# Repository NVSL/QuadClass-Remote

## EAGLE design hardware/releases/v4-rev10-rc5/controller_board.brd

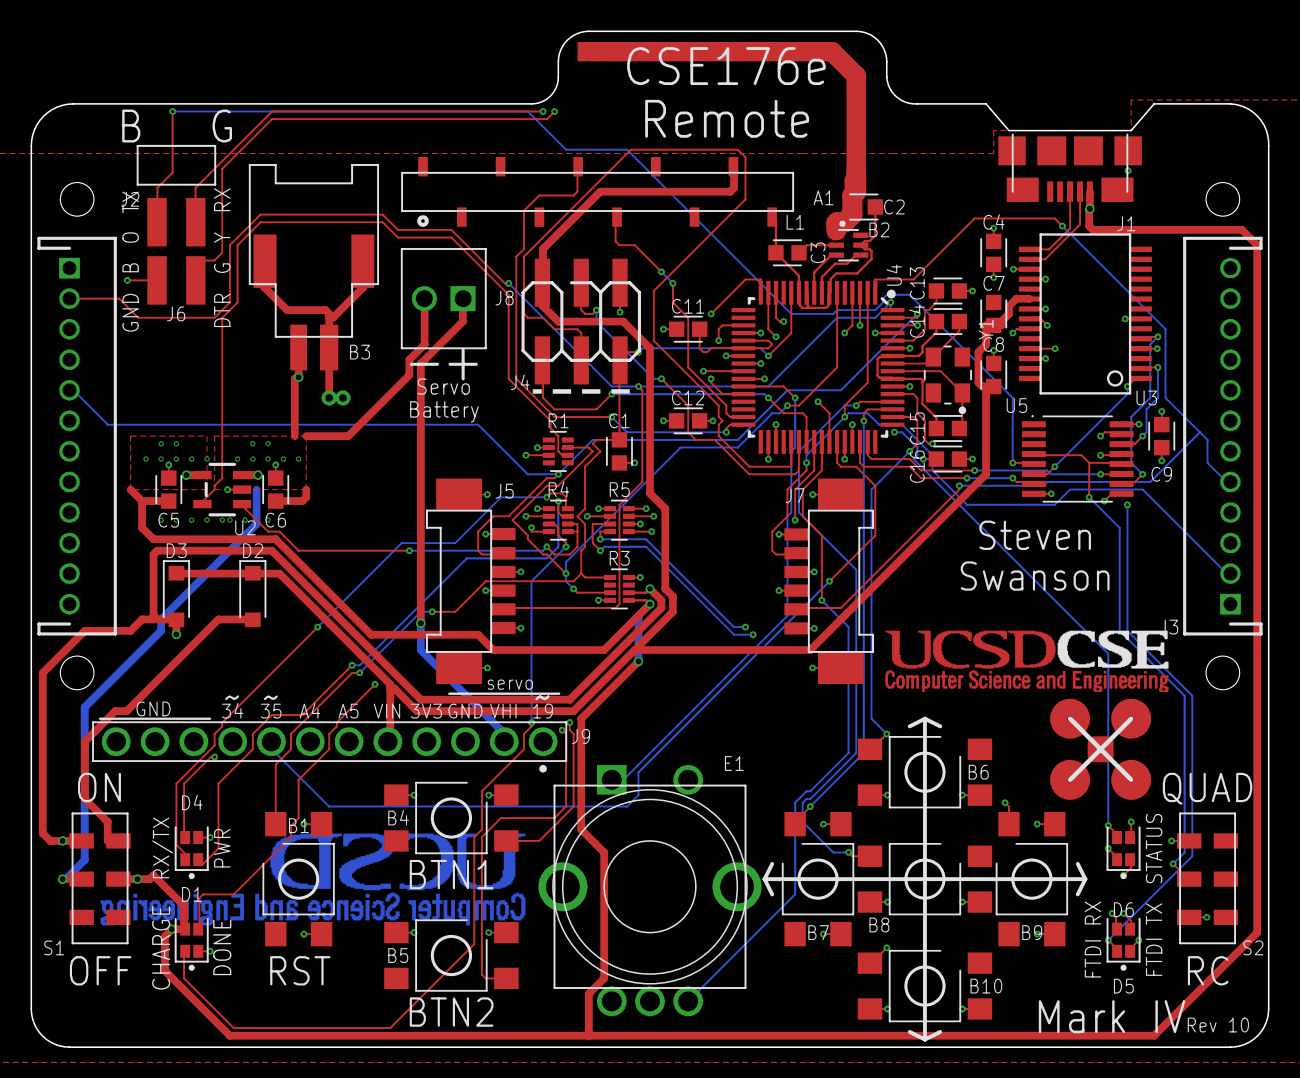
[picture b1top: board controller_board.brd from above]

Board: 4 copper layers, 81.0 x 66.5 mm, 86 parts (1 on the bottom side), 70 nets.

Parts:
A1: ANTENNA-BOARD-REV; ANT_PCB_2.4GHZ_NRF8001_1.6MM_1OZ_REV
B1, B4, B5, B6, B7, B8, B9, B10: PUSHBUTTON_-4.5X4.5; 4.5MM_TACTILE_SWITCH_TL3305AF160QG
B2: BALUN0805; BALUN
B3: BATTERY-SMD; MOLEX-BATTERY-CONNECTOR-SMD-51005-2P
C1, C8, C9: 0.1uF; CAPC1608X100
C2: 0.75pF; CAPC1608X100
C3: 22pF; CAPC1608X100
C4, C11, C12, C13, C16: 1uF; CAPC1608X100
C5, C6, C7: 10uF; CAPC1608X100
C14, C15: 12pF; CAPC1608X100
D1, D4, D5, D6: LED-2X-GREEN/RED-1.6X1.5MM; LED-2X-LITE-ON-1.6MMX1.5MM
D2, D3: 360mV; SODFL3516X96
E1: ROTARY-ENCODER-W/BUTTON-BOURNS-PEC12R-4217F; BOURNS-PEC12R
E$1, E$2: FRSKY-TARANIS-GIMBAL
F1: SHORT
J1: USB-MICROA-AMPHENOL-10118192-0001LF; USB-MICROA-10118192-0001LF
J2, J3: 2.4K; JST-13-PTH
J4: AVR_SPI_PRG_6-SMD; 2X3-SMD
J5, J7: FRSKY-GIMBAL-FRYSKY-HALL-EFFECT; MOLEX-0532610671
J6: FTDI-4PIN-RIGHT-ANGLE-SMD; HEADER-2X2-0.1IN-MALE-RIGHT-ANGLE-SMD
J8: HEADER-0.1IN-2POS-SCREW; SCREW-TERMINAL-1X2-2.54MM
J9: HEADER-12POS-0.1IN-FEMALE-TH; HDRVR12W75P254_1X12_3098X254X850B
L1: SPARKFUN_SERLCD_SERIAL_REDUCED-SMD; SPARKFUN_SERLCD_16X2_REDUCED_SMD
R1: 2.2K; RESCAXS50P200X100X45-8
R3: 10K; RESCAXS50P200X100X45-8
R4, R5: 1.5K; RESCAXS50P200X100X45-8
S1, S2: SWITCH-DPDT-300MA-6V-SMD; JS202011JCQN
U2: MCP73831T-2ACI/OT; SOT23-5
U3: FT232RLSSOP; SSOP28DB
U4: ATMEGA128RFA1; QFN-64
U5: DPDT-X2; SOP65P640X110-16
U$1: 700MAH-BATTERY
U$2: QUADCLASS_LOGO_SMALL
U$3: LAYER_LABELS
U$4: 375MAH-BATTERY
U$5: 600MAH-BATTERY
U$6, U$7: CSE
V1, V2, V3, V4, V5, V6, V7, V8, V23, V24, V26, V27, V28, V30, V31, V32, V33, V34, V35, V36, V37, V38: LOCKED-VIA-0.2; VIA-0.2MM
Y1: CRYSTAL-SMD-3X2; OSCCC320X250X85

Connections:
3V3: C4.2, C9.1, C12.1, C16.1, D4.A1, J2.1, J2.4, J3.1, J3.4, J5.3, J5.6, J7.3, J7.6, J9.4, R3.8, R5.5, R5.6, S2.3, U3.4, U3.17, U4.23, U4.34, U4.44, U4.54, U4.59, U4.62, U5.16
19: J9.1, U4.19
34: J9.9, U4.42
35: J9.8, U4.43
A4: J9.7, U4.3
A5: J9.6, U4.4
ANTENNA: A1.FEED, B2.1, C2.1
BAT_SENSE: R1.7, R3.3, U4.6
BCAP: B2.2, C3.2
BPOS: B3.P, C6.1, J8.2, S1.2, U2.3, V6.P1, V30.P1, V31.P1, V32.P1, V33.P1, V34.P1, V36.P1
BTN1/SCL: B4.3, B4.4, U4.25
BTN2/SDA: B5.3, B5.4, U4.26
BTN_CENTER: B9.1, B9.2, U4.53
BTN_DOWN: B10.1, B10.2, U4.28
BTN_LEFT: B7.1, B7.2, U4.51
BTN_RIGHT: B8.1, B8.2, U4.52
BTN_UP: B6.1, B6.2, U4.50
CLK_NEG: C15.1, U4.56, Y1.1
CLK_POS: C14.1, U4.57, Y1.3
DTR: U3.2, U5.14
DTR-0: C1.2, U5.15
DTR-1: J6.DTR, U5.13
E1-A: E1.A, U4.40
E1-B: E1.B, U4.41
E1-BUT: E1.BUTA, U4.27
GND: B1.3, B1.4, B2.5, B4.1, B4.2, B5.1, B5.2, B6.3, B6.4, B7.3, B7.4, B8.3, B8.4, B9.3, B9.4, B10.3, B10.4, C2.2, C3.1, C4.1, C5.2, C6.2, C7.2, C8.2, C9.2, C11.2, C12.2, C13.2, C14.2, C15.2, C16.2, D1.C1, E1.BUTB, E1.C, F1.2, J1.5, J1.6, J1.7, J1.8, J1.9, J1.10, J1.11, J2.3, J2.6, J3.3, J3.6, J4.6, J5.1, J5.4, J5.G1, J5.G2, J6.GND, J7.1, J7.4, J7.G1, J7.G2, J9.3, J9.10, J9.11, J9.12, L1.GND2, R1.2, R1.3, R3.4, R4.1, R4.2, R5.1, R5.2, S2.1, U2.2, U3.7, U3.18, U3.21, U3.25, U3.26, U4.7, U4.10, U4.11, U4.20, U4.24, U4.33, U4.35, U4.45, U4.55, U4.58, U4.61, U5.8, V3.P1, V4.P1, V5.P1, V7.P1, V8.P1, V35.P1, V37.P1, V38.P1
HIGH-I-GND: B3.G, B3.G2, B3.G3, F1.1
HIGH-V: J8.1, J9.2
LCD_RX: L1.RXI, U4.32
LCD_TX: L1.TX0, U4.31
MISO: J4.1, U4.39
MOSI: J4.4, U4.38
unnamed: D1.A1, R4.4
unnamed: D1.C2, R4.3
unnamed: D5.A1, R5.3
unnamed: D6.C2, R5.8
unnamed: D6.C1, R5.7
unnamed: D4.C1, R4.7
unnamed: D5.A2, R5.4
unnamed: D6.A2, U4.14
unnamed: D6.A1, U4.15
unnamed: R4.5, R4.6, U2.1
unnamed: R1.6, U2.5
unnamed: D4.C2, R4.8
unnamed: D2.2, S1.7
unnamed: C11.1, U4.21, U4.22
unnamed: C13.1, U4.60
PITCH: J3.V, J7.5, U4.2
PROG_SEL: S2.2, U5.4, U5.12
RESET: B1.1, B1.2, C1.1, J4.5, R3.1, U4.12
RF: D4.A2, U4.16
RF_N: B2.3, U4.9
RF_P: B2.4, U4.8
ROLL: J3.H, J7.2, U4.1
RXI: U3.5, U5.10
RXI-0: U4.47, U5.11
RXI-1: J6.RXI, U5.9
RXLED: D5.C2, U3.22
SCK: J4.3, U4.37
THROTTLE: J2.V, J5.5, U4.64
TXLED: D5.C1, U3.23
TXO: U3.1, U5.6
TXO-0: U4.46, U5.7
TXO-1: J6.TXO, U5.5
USB_D_N: J1.2, U3.16
USB_D_P: J1.3, U3.15
VBAT: D3.2, R3.6, S1.3
VBUS: C5.1, D1.A2, J1.1, R3.5, S1.6, U2.4, V1.P1, V2.P1, V23.P1, V24.P1, V26.P1, V27.P1, V28.P1
VIN: C7.1, C8.1, D2.1, D3.1, J4.2, J9.5, L1.RAW, U3.20
YAW: J2.H, J5.2, U4.63

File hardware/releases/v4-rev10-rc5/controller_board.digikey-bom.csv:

DIGIKEY,CKN10723CT-ND,10,2,v4-rev10-rc5/controller_board.sch,RemoteParts:SWITCH-DPDT:-300MA-6V-SMD,
DIGIKEY,ATMEGA128RFA1-ZU-ND ,5,1,v4-rev10-rc5/controller_board.sch,quadparts_prebuilt:ATMEGA128RFA1:,
DIGIKEY,1276-1182-1-ND,25,5,v4-rev10-rc5/controller_board.sch,quadparts_prebuilt:CAPACITOR-NP_:SMD-0603_CERAMIC-1UF,1uF
DIGIKEY,535-9134-1-ND,5,1,v4-rev10-rc5/controller_board.sch,quadparts_prebuilt:CRYSTAL:-SMD-3X2,CRYSTAL-SMD-3X2
ALIBABA,https://www.alibaba.com/product-detail/Molex-51005-51006-2-p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,5,1,v4-rev10-rc5/controller_board.sch,quadparts_prebuilt:BATTERY:-SMD,BATTERY-SMD
DIGIKEY,S5641-ND,5,1,v4-rev10-rc5/controller_board.sch,RemoteParts:SPARKFUN_SERLCD_SERIAL_REDUCED:-SMD,SPARKFUN_SERLCD_SERIAL_REDUCED-SMD
DIGIKEY,CRS08QMCT-ND,10,2,v4-rev10-rc5/controller_board.sch,quadparts_prebuilt:DIODE-SCHOTTKY_:-SMD-SOD123,360mV
DIGIKEY,311-3843-1-ND,5,1,v4-rev10-rc5/controller_board.sch,quadparts_prebuilt:CAPACITOR-NP_:SMD-0603_CERAMIC-0.75PF,0.75pF
DIGIKEY,609-3487-2-ND,5,1,v4-rev10-rc5/controller_board.sch,quadparts_prebuilt:AVR_SPI_PRG_6:-SMD,AVR_SPI_PRG_6-SMD
DIGIKEY,PEC12R-4220F-S0024-ND,5,1,v4-rev10-rc5/controller_board.sch,RemoteParts:ROTARY-ENCODER-W/BUTTON:-BOURNS-PEC12R-4217F,
DIGIKEY,MCP73831T-2ACI/OTCT-ND,5,1,v4-rev10-rc5/controller_board.sch,RemoteParts:MCP73831/2:,MCP73831T-2ACI/OT
DIGIKEY,478-11384-1-ND,5,1,v4-rev10-rc5/controller_board.sch,quadparts_prebuilt:CAPACITOR-NP_:SMD-0603_CERAMIC-22PF,22pF
DIGIKEY,Y10103CT-ND,5,1,v4-rev10-rc5/controller_board.sch,quadparts_prebuilt:RESISTOR-PACK-4X:-10K,10K
SPARKFUN,LCD-14072,5,1,v4-rev10-rc5/controller_board.sch,RemoteParts:SPARKFUN_SERLCD_SERIAL_REDUCED:-SMD,SPARKFUN_SERLCD_SERIAL_REDUCED-SMD
DIGIKEY,160-2252-1-ND,20,4,v4-rev10-rc5/controller_board.sch,RemoteParts:LED-2X:-GREEN/RED-1.6X1.5MM,LED-2X-GREEN/RED-1.6X1.5MM
DIGIKEY,399-1095-1-ND,15,3,v4-rev10-rc5/controller_board.sch,quadparts_prebuilt:CAPACITOR-NP_:SMD-0603_CERAMIC-0.1UF,0.1uF
DIGIKEY,609-4613-1-ND ,5,1,v4-rev10-rc5/controller_board.sch,RemoteParts:USB:-MICROA-AMPHENOL-10118192-0001LF,
DIGIKEY,EG5350CT-ND,40,8,v4-rev10-rc5/controller_board.sch,quadparts_prebuilt:PUSHBUTTON_:-4.5X4.5,PUSHBUTTON_-4.5X4.5
DIGIKEY,ED10561-ND,5,1,v4-rev10-rc5/controller_board.sch,RemoteParts:HEADER-0.1IN-2POS:-SCREW,
DIGIKEY,SAM15344-ND,5,1,v4-rev10-rc5/controller_board.sch,quadparts_prebuilt:FTDI-4PIN:-RIGHT-ANGLE-SMD,
DIGIKEY,768-1007-1-ND ,5,1,v4-rev10-rc5/controller_board.sch,RemoteParts:FT232RL:SSOP,
DIGIKEY,Y10222CT-ND,5,1,v4-rev10-rc5/controller_board.sch,quadparts_prebuilt:RESISTOR-PACK-4X:-2.2K,2.2K
DIGIKEY,1722-1241-ND,5,1,v4-rev10-rc5/controller_board.sch,RemoteParts:ROTARY-ENCODER-W/BUTTON:-BOURNS-PEC12R-4217F,
DIGIKEY,Y10152CT-ND,10,2,v4-rev10-rc5/controller_board.sch,quadparts_prebuilt:RESISTOR-PACK-4X:-1.5K,1.5K
DIGIKEY,1276-1119-1-ND,15,3,v4-rev10-rc5/controller_board.sch,quadparts_prebuilt:CAPACITOR-NP_:SMD-0603_CERAMIC-10UF,10uF
DIGIKEY,568-5300-1-ND,5,1,v4-rev10-rc5/controller_board.sch,RemoteParts:DPDT-X2:,
NA,NA,120,24,v4-rev10-rc5/controller_board.sch,RemoteParts:SHORT:,
DIGIKEY,WM7624CT-ND,10,2,v4-rev10-rc5/controller_board.sch,RemoteParts:FRSKY-GIMBAL:-FRYSKY-HALL-EFFECT,
DIGIKEY,720-1655-1-ND,10,2,v4-rev10-rc5/controller_board.sch,quadparts_prebuilt:CAPACITOR-NP_:SMD-0603_CERAMIC-12PF,12pF
DIGIKEY,732-2230-1-ND,5,1,v4-rev10-rc5/controller_board.sch,quadparts_prebuilt:BALUN:0805,
DIGIKEY,A100106-ND,10,2,v4-rev10-rc5/controller_board.sch,RemoteParts:FRSKY-GIMBAL:-FRYSKY,2.4K
DIGIKEY,S6100-ND,5,1,v4-rev10-rc5/controller_board.sch,quadparts_prebuilt:HEADER-12POS:-0.1IN-FEMALE-TH,

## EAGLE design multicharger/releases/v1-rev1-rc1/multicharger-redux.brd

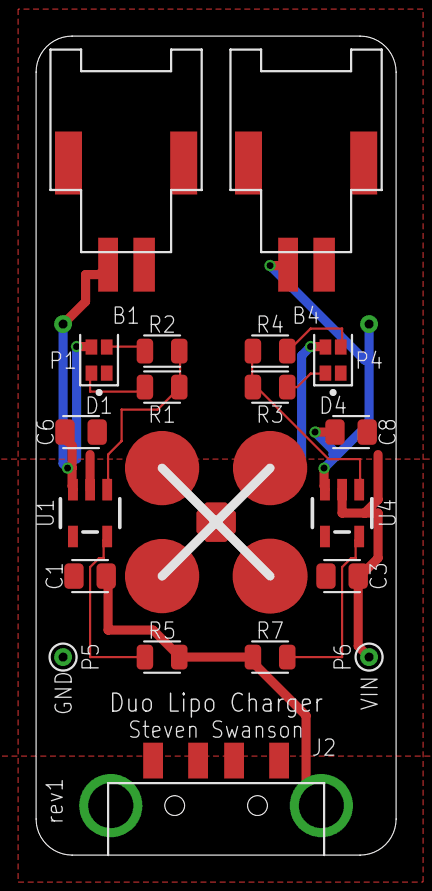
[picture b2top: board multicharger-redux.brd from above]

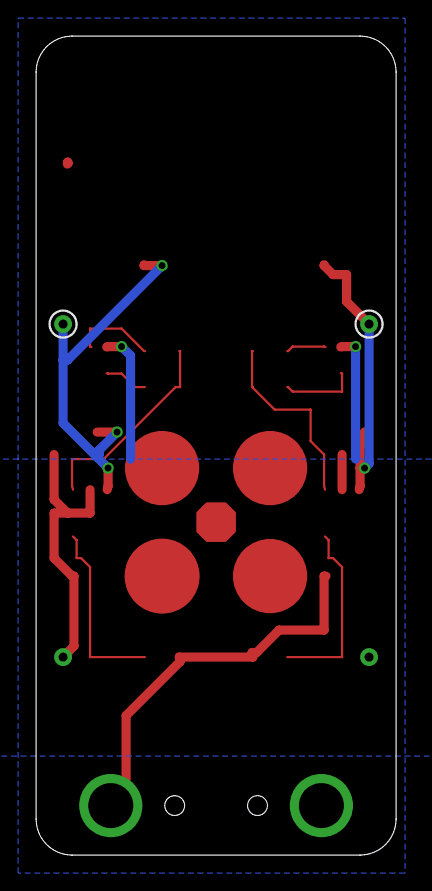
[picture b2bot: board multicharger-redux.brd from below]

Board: 4 copper layers, 20.0 x 45.5 mm, 22 parts (2 on the bottom side), 12 nets.

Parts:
B1, B4: BATTERY-SMD; MOLEX-BATTERY-CONNECTOR-SMD-51005-2P
C1, C3, C6, C8: 10uF; CAPC2012X140_HS
D1, D4: LED-2X-GREEN/RED-1.6X1.5MM; LED-2X-LITE-ON-1.6MMX1.5MM
J2: USB-A-SMD-KEYSTONE-931; USB-A-KEYSTONE-931
P1, P4, P5, P6: TEST-POINT-1MM; TEST-POINT-1MM-VIA
R1, R2, R3, R4: 1.2K; RESC2012X60_HS
R5, R7: 2K; RESC2012X60_HS
U1, U4: MCP73831T-2ACI/OT; SOT23-5
U$2: QUADCLASS_LOGO

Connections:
BPOS1: B1.P, C6.1, P1.T, U1.3
BPOS4: B4.P, C8.1, P4.T, U4.3
GND: B1.G, B1.G2, B1.G3, B4.G, B4.G2, B4.G3, C1.2, C3.2, C6.2, C8.2, D1.C1, D4.C1, J2.G1, J2.G2, P6.T, R5.2, R7.2, U1.2, U4.2
unnamed: D1.A1, R2.1
unnamed: D1.C2, R1.1
unnamed: R1.2, R2.2, U1.1
unnamed: R5.1, U1.5
unnamed: R3.2, R4.2, U4.1
unnamed: R7.1, U4.5
unnamed: D4.A1, R4.1
unnamed: D4.C2, R3.1
VIN: C1.1, C3.1, D1.A2, D4.A2, J2.1, P5.T, U1.4, U4.4

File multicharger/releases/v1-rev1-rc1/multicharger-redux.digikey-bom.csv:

DIGIKEY,36-931-ND,5,1,v1-rev1-rc1/multicharger-redux.sch,RemoteParts:USB:-A-SMD-KEYSTONE-931,USB-A-SMD-KEYSTONE-931
DIGIKEY,MCP73831T-2ACI/OTCT-ND,10,2,v1-rev1-rc1/multicharger-redux.sch,RemoteParts:MCP73831/2:,MCP73831T-2ACI/OT
DIGIKEY,490-5523-1-ND,20,4,v1-rev1-rc1/multicharger-redux.sch,quadparts_prebuilt:CAPACITOR-NP_:SMD-2012-0805_CERAMIC-10UF,10uF
NA,NA,20,4,v1-rev1-rc1/multicharger-redux.sch,RemoteParts:TEST-POINT:-1MM,TEST-POINT-1MM
ALIBABA,https://www.alibaba.com/product-detail/Molex-51005-51006-2-p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,10,2,v1-rev1-rc1/multicharger-redux.sch,quadparts_prebuilt:BATTERY:-SMD,
DIGIKEY,311-1.20KCRCT-ND,20,4,v1-rev1-rc1/multicharger-redux.sch,quadparts_prebuilt:RESISTOR_:SMD-2012-0805-1.2K,1.2K
DIGIKEY,YAG3700CT-ND,10,2,v1-rev1-rc1/multicharger-redux.sch,quadparts_prebuilt:RESISTOR_:SMD-2012-0805-2K,2K
DIGIKEY,160-2252-1-ND,10,2,v1-rev1-rc1/multicharger-redux.sch,RemoteParts:LED-2X:-GREEN/RED-1.6X1.5MM,LED-2X-GREEN/RED-1.6X1.5MM
